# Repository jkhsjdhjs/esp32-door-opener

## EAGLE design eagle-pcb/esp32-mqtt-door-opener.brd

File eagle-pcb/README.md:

## Used Libraries
- [AZ1084C Series LOD Voltage Regulator](https://github.com/jkhsjdhjs/eagle-libraries/blob/master/AZ1084C.lbr)
- [LBA710 60V Dual Single-Pole OptoMOS® Relay](https://github.com/jkhsjdhjs/eagle-libraries/blob/master/LBA710.lbr)
- [Macro Yau's ESP32 Library](https://github.com/MacroYau/MacroYau-EAGLE-Libraries/blob/master/esp32.lbr)
- [TL2230 Series Sub-Miniature Pushbutton Switch](https://github.com/jkhsjdhjs/eagle-libraries/blob/master/TL2230.lbr)
- con-jack
- con-wago-500
- frames
- led
- optocoupler
- pinhead
- rcl
- rectifier
- switch-omron
- transistor-fet

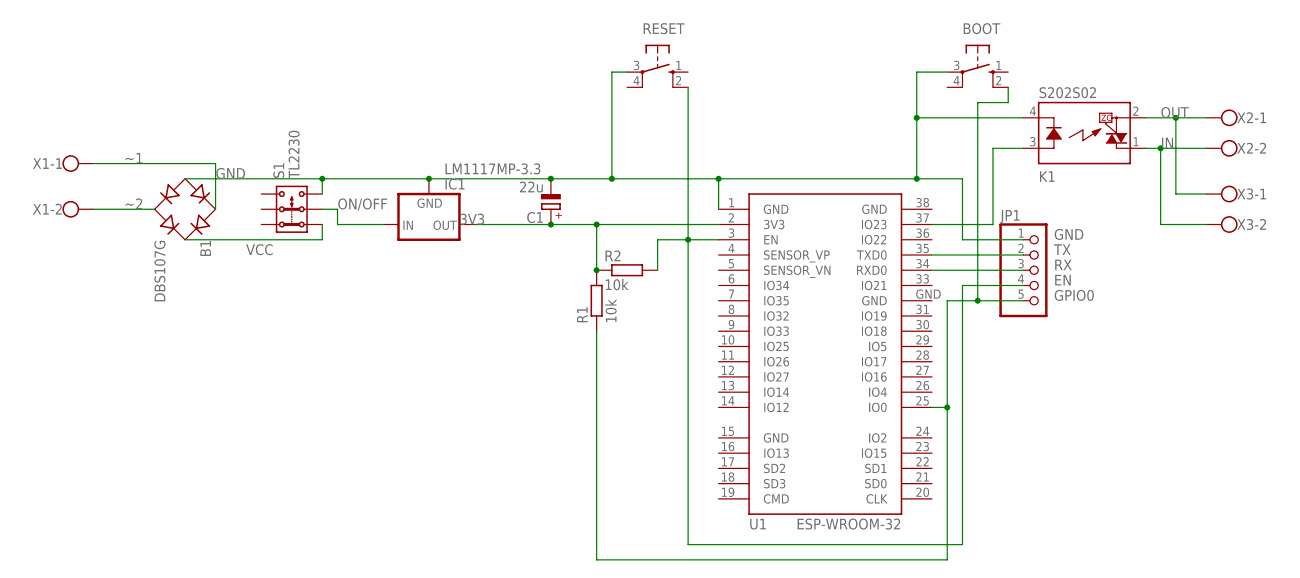
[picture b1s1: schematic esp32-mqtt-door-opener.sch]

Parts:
B1: DBS107G; DBS
BOOT: 10-XX; B3F-10XX
C1: 22u; SMC_C
IC1: LM1117MP-3.3; SOT223
JP1: PINHD-1X5; 1X05
K1: S202S02; S*02S02
R1, R2: 10k; R1206
RESET: 10-XX; B3F-10XX
S1: TL2230
U1: ESP-WROOM-32
X1, X2, X3: W237-102

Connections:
3V3: C1.+, IC1.2 (OUT), IC1.4 (OUT), R1.2, R2.1, U1.2 (3V3)
EN: JP1.4, R2.2, RESET.2 (S1), U1.3 (EN)
GND: B1.-, BOOT.3, C1.-, IC1.1 (GND), JP1.1, K1.4 (K), RESET.3, S1.6 (3.2), U1.1 (GND), U1.15 (GND), U1.38 (GND), U1.GND
GPIO0: BOOT.2 (S1), JP1.5, R1.1, U1.25 (IO0)
GPIO23: K1.3 (A), U1.37 (IO23)
IN: K1.1 (DS1), X2.2, X3.2
ON/OFF: IC1.3 (IN), S1.5 (2.2)
OUT: K1.2 (DS2), X2.1, X3.1
RX: JP1.3, U1.34 (RXD0)
TX: JP1.2, U1.35 (TXD0)
VCC: B1.+, S1.4 (1.2)
~1: B1.AC1, X1.1
~2: B1.AC2, X1.2

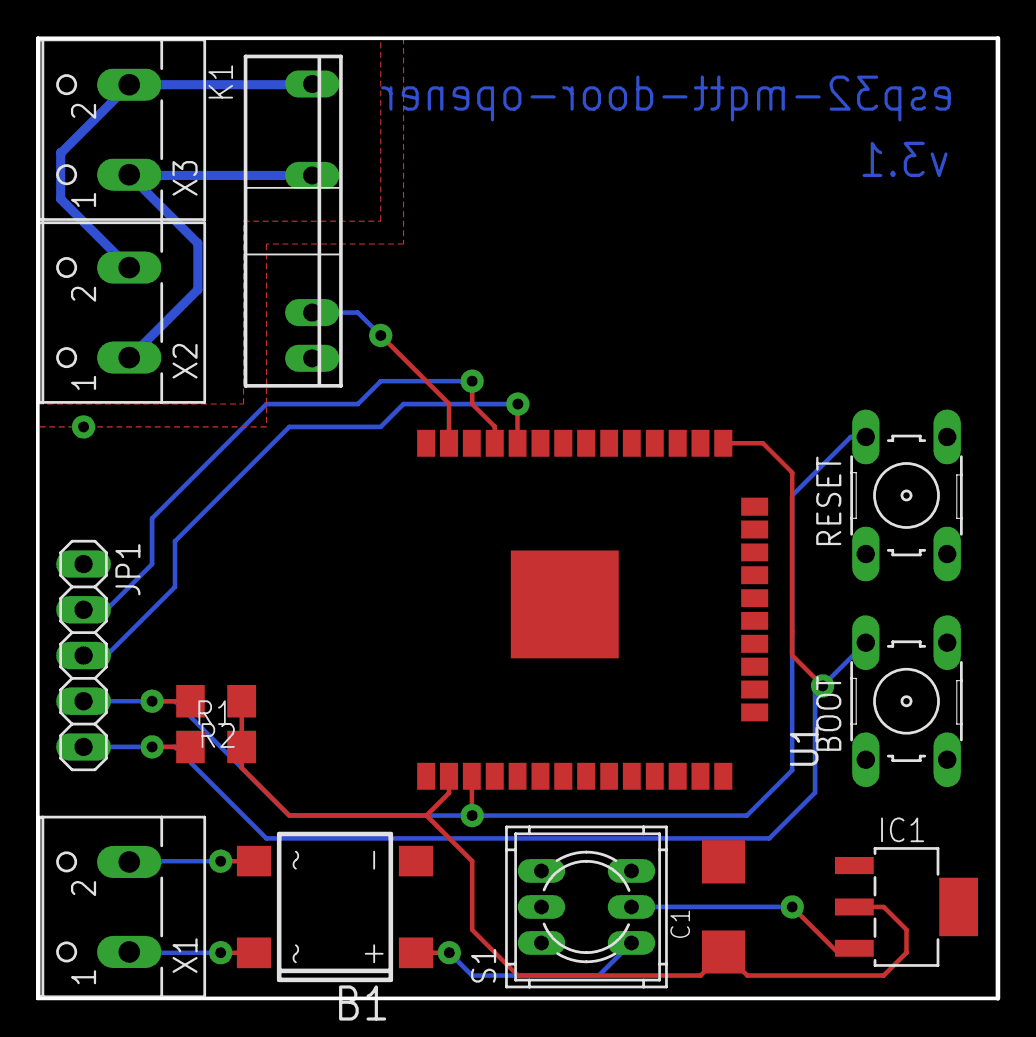
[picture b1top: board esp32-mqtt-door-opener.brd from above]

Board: 2 copper layers, 53.3 x 53.3 mm, 14 parts (0 on the bottom side), 13 nets.

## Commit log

2019-10-31 add pcb schematic + board add 'mqtt' to default value of HOSTNAME in Kconfig
2019-10-31 pcb: add missing trace
2019-10-31 pcb: stretch power source lane
2019-11-01 pcb: change wire widths and move rectifier a bit
2019-11-01 pcb: minor improvements to trace routing
2019-11-05 pcb: revision 3.1 with rubout incoming
2019-12-26 replace hardcoded gpio ports with config variable
2021-06-19 pcb: revise schematic to 4.0
2021-06-20 pcb: use 330 ohm resistors instead of 390 + use ESP32-WROOM-32D
2021-06-21 gitignore: move some lines to new .gitignore file + ignore autorouter files
2021-06-21 pcb: adjust some labels

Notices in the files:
parts and their libraries:
esp32: Creative Commons Attribution-ShareAlike 4.0 International
SparkFun-Aesthetics: Licensing: Creative Commons ShareAlike 4.0 International - https://creativecommons.org/licenses/by-sa/4.0
